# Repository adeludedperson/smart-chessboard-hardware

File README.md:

# Smart Chessboard: hardware

A 64-square chessboard that detects where pieces stand with one Hall-effect sensor per square, read by an ESP32 and sent out over USB serial or Wi-Fi.

*Render of the enclosure design for the sensing board (the renders call it "v5"). Renders, not photos.*

## What it is for

Tournament chess is played on a real board, but engines, training tools and online opponents all live on a screen. This board joins the two. You move real pieces, the board reads the position, and a chess app on a computer treats it as your move: against an engine, in a training exercise, or in a live Lichess game. The reply shows in the app and you play it on the board.

My brother plays over-the-board tournaments and practises on this board every day.

## How it works

1. **A magnet in each piece.** Each piece carries a 10 x 3 mm N35 neodymium disc in its base.
2. **A sensor under each square.** An A3144 Hall-effect switch sits at the centre of each 50 mm square, on the underside of the PCB, bent flat. The A3144 responds to one magnet pole only, so every magnet is glued with its working face down.
3. **10k pull-ups.** Each sensor output has a 10 kΩ pull-up to 3.3 V. A magnet pulls the line low, so an occupied square reads as 0.
4. **74HC165 shift registers.** Two 74HC165 parallel-in shift registers per board latch 16 sensor states at once. The registers run at 3.3 V and the sensors at 5 V, so the ESP32 never sees 5 V on a data line.
5. **Four identical boards.** The board is four 200 x 200 mm quadrant PCBs of 16 squares each, chained J2 to J1 with 6-wire jumpers. The chain carries power and signals, and the four boards together form one 64-bit shift chain.
6. **Three wires to the ESP32.** The ESP32 drives /PL (GPIO25) and CP (GPIO26) and reads the chain's data out on GPIO27. GPIO14 injects a test pattern into the chain for the gate test.
7. **USB serial or Wi-Fi out.** The firmware sends one line per frame, `raw = 0x` followed by 16 hex digits, about 50 times a second, over USB serial, or over USB and a Wi-Fi TCP connection at the same time.

In the enclosure design, the boards hang component side down on 20 mm standoffs between two 4 mm MDF sheets. The magnet sits 7.1 mm from the sensor: 4.0 mm MDF, 1.0 mm air gap, 1.6 mm PCB and about 0.5 mm into the sensor package. Dimensions, cut list, drilling, jumper lengths and assembly order are in [docs/MECHANICAL.md](docs/MECHANICAL.md).

## Hardware

| Board | What it is | Status |
|---|---|---|
| [Quadrant v1](pcb/quadrant/) | 200 x 200 mm, 2-layer, all through-hole. 16 A3144, 16 x 10k, 2 x 74HC165 (DIP-16), 10 x 100 nF, two 1x6 headers. 50 mm squares. | Fabricated (5 boards). Four assembled, chained and tested. |
| [Quadrant v2](pcb/quadrant_v2/) | 132 x 132 mm, 2-layer, all SMT for factory assembly. 33 mm squares, UHE4913G omnipolar Hall sensor and WS2812C-2020 LED per square, keyed 2x6 ribbon connectors. | Design only. DRC-clean, gerbers exported. Not ordered as of 2026-09-01. |
| [Hub v2](pcb/hub_v2/) | 88 x 60 mm. ESP32-WROOM-32E module, Micro-USB, CH340C USB-serial, TP4056 charger and 18650 holder (protected cell required). | Design only. DRC-clean, gerbers exported. Not ordered as of 2026-09-01. |
| [Hub v3 USB-C](pcb/hub_v3_usbc/) | Hub v2 with the Micro-USB port replaced by USB-C and 5.1 kΩ CC pull-downs. | Design only. DRC-clean, gerbers exported. No order recorded. |
| [RFID test rig](pcb/rfid_test_rig/) | 80 x 92 mm, 4-layer, 2x2 squares. Tests 125 kHz antenna coils under each square, an EM4095 reader and 74HC4851 muxes, toward identifying pieces as well as detecting them. | Design only. DRC-clean, gerbers exported. No order recorded. |

Notes for builders:

- The A3144 parts used on the v1 boards were mirror-pinout clones and had to go in rotated 180 degrees from a genuine part. Read [pcb/quadrant/assembly/ASSEMBLY_NOTES.md](pcb/quadrant/assembly/ASSEMBLY_NOTES.md) and solder one sensor at S0 and test it with a magnet before soldering the other 15.
- The v1 board is generated from one number, the square size. To regenerate it, follow [pcb/quadrant/README.md](pcb/quadrant/README.md).
- Design notes: [pcb/DESIGN.md](pcb/DESIGN.md) (v1), [pcb/DESIGN_V2.md](pcb/DESIGN_V2.md) (v2 compact board), [pcb/DESIGN_V3_RFID.md](pcb/DESIGN_V3_RFID.md) (RFID piece recognition, paper design).
- Per-board parts list: [pcb/quadrant/assembly/chess_quadrant_bom.csv](pcb/quadrant/assembly/chess_quadrant_bom.csv). Fasteners and wood: [docs/MECHANICAL.md](docs/MECHANICAL.md) sections 4 and 6.
- Datasheets: [A3144](https://www.allegromicro.com/en/products/sense/switches-and-latches) (Allegro, discontinued; the boards use clones), [SN74HC165](https://www.ti.com/product/SN74HC165) (TI), [ESP32](https://www.espressif.com/en/products/modules/esp32) (Espressif).

## Firmware

Arduino sketches for an ESP32 dev board, one folder per sketch in [firmware/](firmware/).

| Sketch | Use it for |
|---|---|
| `board_stream` | Main firmware, USB only. Measures the chain length at boot, streams frames at about 50 per second, re-runs the gate test every 5 s. |
| `board_stream_wifi` | Same sensing code, plus Wi-Fi: every line goes to USB serial and to a TCP connection. Adds over-the-air updates and a status page on port 80. |
| `read_audit` | Reads the board four ways and compares them. Run it before blaming a sensor. |
| `chain_len` | Counts the shift-register stages in the chain. The gate test passes on a chain that is too short; this finds it. |
| `quadrant_test`, `quadrant_diag` | Single-board bring-up. |
| `quadrant_diag32`, `quadrant_diag64` | 2-board and 4-board gate tests. |
| `dgt_clock_bridge` | A second ESP32 that connects a DGT 3000 chess clock through its 3.5 mm jack, over USB serial and Wi-Fi. |
| `adc_diag`, `rail_test`, `short_meter`, `wiring_diag`, `sensor_test`, `quad_probe`, `quadrant_diag2`, `quadrant_diag3` | One-off diagnostic rigs from bring-up. |

The gate test shifts all 0s and then all 1s through the chain and prints `CHAIN64: PASS` or `FAIL`. An all-clear frame reads the same as a dead chain, so check the gate result before trusting a reading.

[firmware/tools/](firmware/tools/) has Python serial readers and live dashboards for bring-up (no dependencies; edit the port at the top of each script).

### Flash over USB

You need `arduino-cli` with the ESP32 core. Close any program reading the serial port first.

```bash
cd firmware
arduino-cli compile --fqbn esp32:esp32:esp32 board_stream
arduino-cli upload -p <your-port> --fqbn esp32:esp32:esp32 board_stream
```

On macOS the port looks like `/dev/cu.usbserial-0001`.

### Set up Wi-Fi

1. Copy the template: `cp firmware/board_stream_wifi/secrets.example.h firmware/board_stream_wifi/secrets.h`
2. In `secrets.h`, set `WIFI_SSID` and `WIFI_PASS` (2.4 GHz networks only), `SCB_HOST` (the mDNS name of the computer that receives the stream) and `SCB_FALLBACK_IP` (that computer's address, used only on first boot). `secrets.h` is in `.gitignore`.
3. Flash once over USB: `firmware/board_stream_wifi/flash.sh <your-port>`
4. Power the ESP32 from a 5 V USB charger, 2 A or more.
5. Later updates go over Wi-Fi: `firmware/board_stream_wifi/ota.sh`

The board answers at `chess-sensor.local`, with a status page showing Wi-Fi signal, connection state and the last gate result. The helper scripts are written for macOS. The clock bridge uses the same steps in `firmware/dgt_clock_bridge/`.

## Status

- **2026-11-14:** In daily use for tournament practice.
- **2026-08-24:** Five v1 quadrant PCBs fabricated. Four assembled and chained into a 64-square board that passes the 64-stage gate test, detects a full set of 32 pieces, and streams over Wi-Fi. The wooden frame and playing surface in [docs/MECHANICAL.md](docs/MECHANICAL.md) were still listed as pending on this date.
- **2026-09-26:** DGT 3000 clock bridge tested on a real clock.
- **2026-09-26:** Quadrant v2, hub v2, hub v3 and the RFID test rig are designed and DRC-clean. No fabrication of these boards is recorded.

## Software

The board feeds a separate chess app that runs on a computer. It plays against engines (Stockfish and Maia), has training modes, and plays Lichess games from the physical board. That app is not in this repository.

## Repository layout

| Path | Contents |
|---|---|
| [pcb/](pcb/) | KiCad boards, generator and routing scripts, design notes, gerbers, BOMs, plots |
| [pcb/quadrant/assembly/](pcb/quadrant/assembly/) | Assembly notes, solder job sheets, pick-and-place, BOM |
| [firmware/](firmware/) | ESP32 sketches and the [firmware README](firmware/README.md) |
| [firmware/tools/](firmware/tools/) | Python serial readers and bring-up dashboards |
| [docs/MECHANICAL.md](docs/MECHANICAL.md) | Enclosure stack-up, cut list, drilling, wiring lengths, assembly order |
| [docs/WORKING_SETUP_2026-08-18.md](docs/WORKING_SETUP_2026-08-18.md) | Exact wiring and bit order of the first working 2-board chain |
| [docs/stickers/](docs/stickers/) | Printable 440 x 440 mm board decals, their generator and how to apply them |
| [renders/](renders/) | Renders of the board designs, including earlier LED concepts that were not built |
| [diagrams/](diagrams/) | Generator for the single-sensor test wiring diagram |
| [sim/](sim/) | SPICE model for the `short_meter` rig |

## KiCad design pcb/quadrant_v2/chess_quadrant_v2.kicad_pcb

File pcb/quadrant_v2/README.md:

# V2 Compact Quadrant — 33mm pitch, all-SMT, JLCPCB-assemblable

Generated board. **DRC clean (0 violations, 0 unconnected).**
469+ tracks, 431 vias, fully routed by `../generate_quadrant_v2.py`.

## What it is

132×132mm, 2-layer. One quadrant = 4×4 squares of the compact chessboard.
Order **20 pcs** (5 board-sets + spares), all identical.

Per square: UHE4913G omnipolar hall (C86815) at exact square center,
WS2812C-2020 RGB LED (C2976072) offset +8/+8mm, 100nF each. 2× 74HC165
(C22384789) chain all 16 sensors into the board-wide 64-bit shift chain.

## Regenerate

```
~/Applications/KiCad/KiCad.app/Contents/Frameworks/Python.framework/Versions/Current/bin/python3.9 \
    ../generate_quadrant_v2.py            # emits .kicad_pcb + BOM.csv + positions.csv
~/Applications/KiCad/KiCad.app/Contents/MacOS/kicad-cli pcb drc --severity-error \
    --format json -o drc_v2.json chess_quadrant_v2.kicad_pcb
~/Applications/KiCad/KiCad.app/Contents/MacOS/kicad-cli pcb export gerbers -o gerbers/ \
    --layers F.Cu,B.Cu,F.Paste,B.Paste,F.SilkS,B.SilkS,F.Mask,B.Mask,Edge.Cuts \
    chess_quadrant_v2.kicad_pcb
~/Applications/KiCad/KiCad.app/Contents/MacOS/kicad-cli pcb export drill -o gerbers/ \
    chess_quadrant_v2.kicad_pcb
```

## Order at JLCPCB

1. Zip `gerbers/`, upload at jlcpcb.com/quote. 132×132mm, 2-layer, 1.6mm, qty 20.
2. Enable "PCB Assembly" (economic, top side). Upload `BOM.csv` + `positions.csv`.
3. In the part-placement preview, CHECK ROTATIONS of U1-U16 (SOT-23), D1-D16
   (LED polarity dot!), U17/U18 pin-1 — JLC's rotation convention can differ
   from KiCad's. Fix in their viewer if a part looks turned.
4. Two BOM lines have no LCSC number yet — pick in JLC's picker:
   - CB1: 1000µF ≥6.3V SMT electrolytic, 8×10mm
   - J1/J2: 2×6 (12-pin) 2.54mm shrouded box header, through-hole
5. LED (C2976072) stock fluctuates; substitute WS2812B-2020 (same footprint/
   pinout) if dry.

## Interconnect (J1 = IN, top edge; J2 = OUT, bottom edge)

2×6 keyed box header + 12-way IDC ribbon. Inner row (board side) carries
signals, outer row is all GND:

| Col (left→right) | 1 | 2 | 3 | 4 | 5 | 6 |
|---|---|---|---|---|---|---|
| Inner | /PL | CP | SER | +5V | +3V3 | LED_DATA |
| Outer | GND | GND | GND | GND | GND | GND |

Chain: hub → J1 of Q1 → (J2 → next J1) ×3. Quadrants tile with alternating
180° rotation so J2/J1 meet at the seams.

## Firmware maps (printed by the generator)

```
CHAIN_ORDER (first bit read -> last) = [15,14,11,10, 2,3,6,7, 13,12,9,8, 0,1,4,5]
LED_CHAIN   (square idx, serpentine) = [0,1,2,3, 7,6,5,4, 8,9,10,11, 15,14,13,12]
```

`CHAIN_ORDER[i]` = which square (0-15, row-major from board origin) produced
the i-th bit shifted out of this quadrant. LED index k in the WS2812 chain
lights square `LED_CHAIN[k]`.

## Still manual / to verify before paying

1. Rotation check in JLC viewer (step 3 above) — the one real risk.
2. Hub PCB (ESP32 + Micro-USB + charger + 18650 holder): DONE and DRC-clean,
   see ../hub_v2/README.md.
3. First article: power one assembled quadrant alone (hub or bench 3V3/5V via
   J1) and run the firmware self-test before building all five sets.

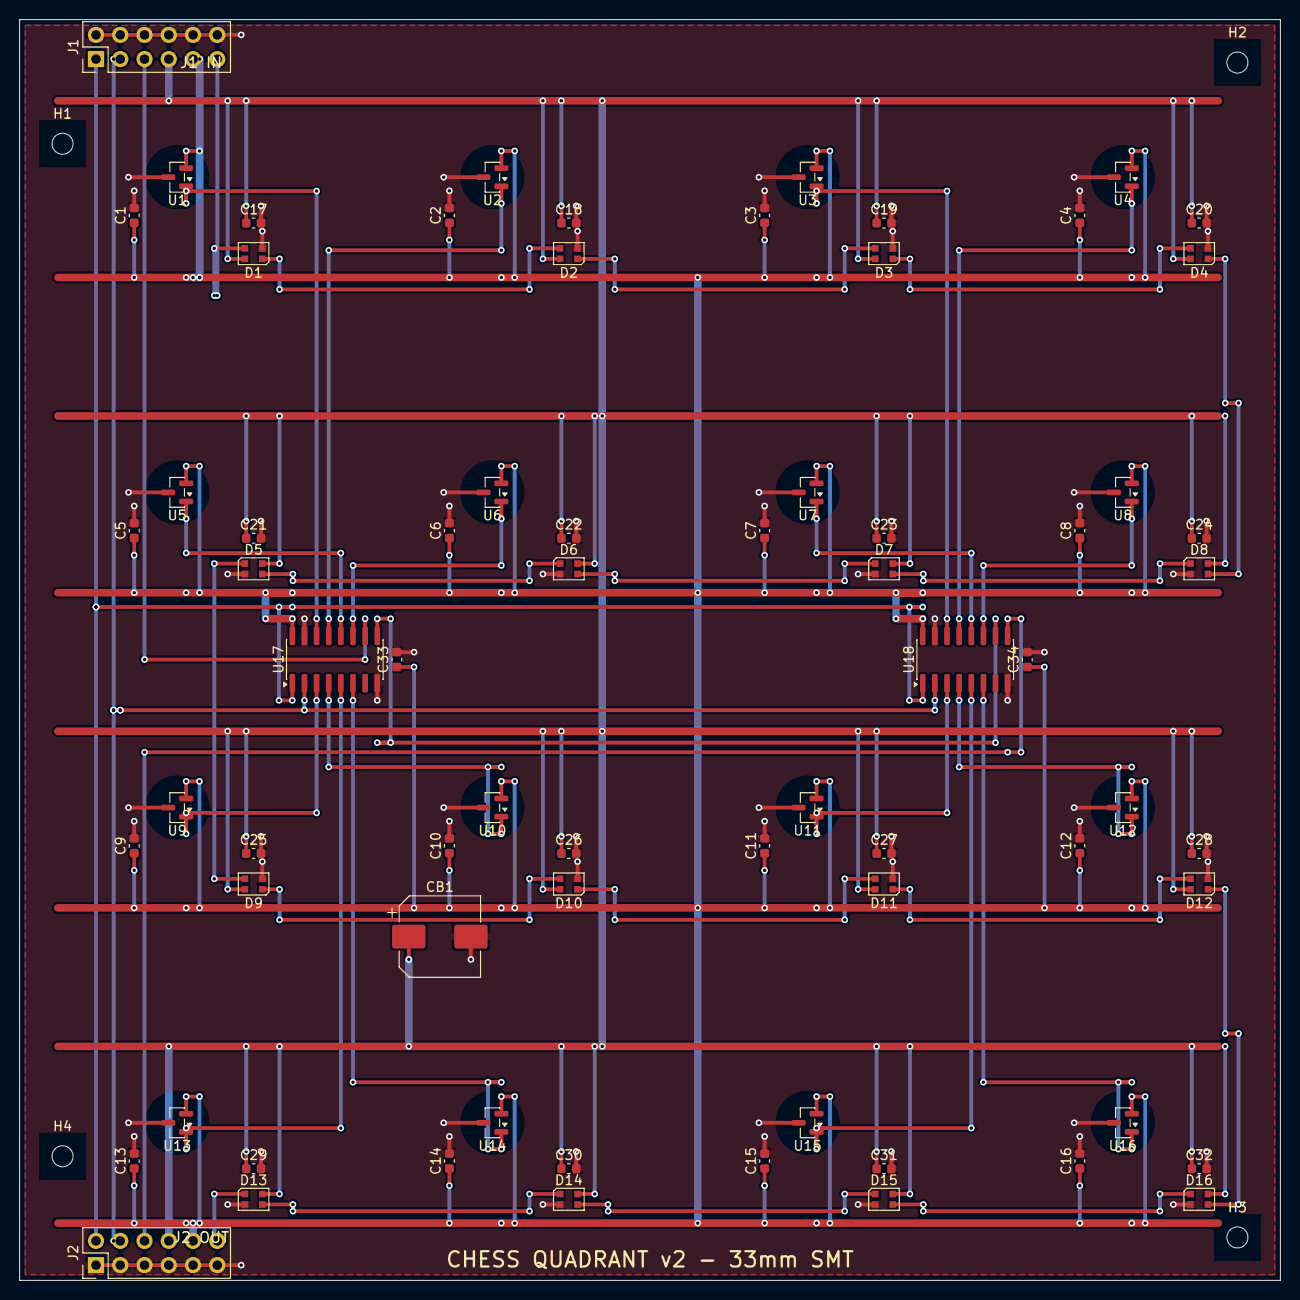
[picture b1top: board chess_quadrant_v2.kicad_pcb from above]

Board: 2 copper layers, 132.0 x 132.0 mm, 75 parts (0 on the bottom side), 41 nets.

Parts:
C1, C2, C3, C4, C5, C6, C7, C8, C9, C10, C11, C12, C13, C14, C15, C16, C17, C18, C19, C20, C21, C22, C23, C24, C25, C26, C27, C28, C29, C30, C31, C32, C33, C34: 100n; C_0603_1608Metric
CB1: 1000u/10V; CP_Elec_8x10
D1, D2, D3, D4, D5, D6, D7, D8, D9, D10, D11, D12, D13, D14, D15, D16: WS2812C-2020; LED_WS2812B-2020_PLCC4_2.0x2.0mm
H1, H2, H3, H4: MountingHole_2.2mm_M2
J1: IN; PinHeader_2x06_P2.54mm_Vertical
J2: OUT; PinHeader_2x06_P2.54mm_Vertical
U1, U2, U3, U4, U5, U6, U7, U8, U9, U10, U11, U12, U13, U14, U15, U16: UHE4913G; SOT-23
U17, U18: 74HC165; SOIC-16_3.9x9.9mm_P1.27mm

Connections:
+3V3: C1.1, C2.1, C3.1, C4.1, C5.1, C6.1, C7.1, C8.1, C9.1, C10.1, C11.1, C12.1, C13.1, C14.1, C15.1, C16.1, C33.1, C34.1, J1.9, J2.10, U1.2, U2.2, U3.2, U4.2, U5.2, U6.2, U7.2, U8.2, U9.2, U10.2, U11.2, U12.2, U13.2, U14.2, U15.2, U16.2, U17.16, U18.16
+5V: C17.1, C18.1, C19.1, C20.1, C21.1, C22.1, C23.1, C24.1, C25.1, C26.1, C27.1, C28.1, C29.1, C30.1, C31.1, C32.1, CB1.1, D1.4, D2.4, D3.4, D4.4, D5.4, D6.4, D7.4, D8.4, D9.4, D10.4, D11.4, D12.4, D13.4, D14.4, D15.4, D16.4, J1.7, J2.8
/PL: J1.1, J2.2, U17.1, U18.1
CP: J1.3, J2.4, U17.2, U18.2
GND: C1.2, C2.2, C3.2, C4.2, C5.2, C6.2, C7.2, C8.2, C9.2, C10.2, C11.2, C12.2, C13.2, C14.2, C15.2, C16.2, C17.2, C18.2, C19.2, C20.2, C21.2, C22.2, C23.2, C24.2, C25.2, C26.2, C27.2, C28.2, C29.2, C30.2, C31.2, C32.2, C33.2, C34.2, CB1.2, D1.2, D2.2, D3.2, D4.2, D5.2, D6.2, D7.2, D8.2, D9.2, D10.2, D11.2, D12.2, D13.2, D14.2, D15.2, D16.2, J1.2, J1.4, J1.6, J1.8, J1.10, J1.12, J2.1, J2.3, J2.5, J2.7, J2.9, J2.11, U1.3, U2.3, U3.3, U4.3, U5.3, U6.3, U7.3, U8.3, U9.3, U10.3, U11.3, U12.3, U13.3, U14.3, U15.3, U16.3, U17.8, U17.15, U18.8, U18.15
LEDD_0: D1.3, J1.11
LEDD_1: D1.1, D2.3
LEDD_2: D2.1, D3.3
LEDD_3: D3.1, D4.3
LEDD_4: D4.1, D8.3
LEDD_5: D7.3, D8.1
LEDD_6: D6.3, D7.1
LEDD_7: D5.3, D6.1
LEDD_8: D5.1, D9.3
LEDD_9: D9.1, D10.3
LEDD_10: D10.1, D11.3
LEDD_11: D11.1, D12.3
LEDD_12: D12.1, D16.3
LEDD_13: D15.3, D16.1
LEDD_14: D14.3, D15.1
LEDD_15: D13.3, D14.1
LEDD_16: D13.1, J2.12
SENS_0: U1.1, U17.14
SENS_1: U2.1, U17.13
SENS_2: U3.1, U18.14
SENS_3: U4.1, U18.13
SENS_4: U5.1, U17.12
SENS_5: U6.1, U17.11
SENS_6: U7.1, U18.12
SENS_7: U8.1, U18.11
SENS_8: U9.1, U17.3
SENS_9: U10.1, U17.4
SENS_10: U11.1, U18.3
SENS_11: U12.1, U18.4
SENS_12: U13.1, U17.5
SENS_13: U14.1, U17.6
SENS_14: U15.1, U18.5
SENS_15: U16.1, U18.6
SER_IN: J1.5, U17.10
SER_MID: U17.9, U18.10
SER_OUT: J2.6, U18.9

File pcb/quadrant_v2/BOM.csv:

Comment,Designator,Footprint,LCSC Part #
1000u/10V,CB1,CP_Elec_8x10,C5246577
100n,"C1,C2,C3,C4,C5,C6,C7,C8,C9,C10,C11,C12,C13,C14,C15,C16,C17,C18,C19,C20,C21,C22,C23,C24,C25,C26,C27,C28,C29,C30,C31,C32,C33,C34",C_0603_1608Metric,C5137636
74HC165,"U17,U18",SOIC-16_3.9x9.9mm_P1.27mm,C22384789
2x6 header,"J1,J2",PinHeader_2x06_P2.54mm_Vertical,C7501277
UHE4913G,"U1,U2,U3,U4,U5,U6,U7,U8,U9,U10,U11,U12,U13,U14,U15,U16",SOT-23,C86815
WS2812C-2020,"D1,D2,D3,D4,D5,D6,D7,D8,D9,D10,D11,D12,D13,D14,D15,D16",LED_WS2812B-2020_PLCC4_2.0x2.0mm,C52917434

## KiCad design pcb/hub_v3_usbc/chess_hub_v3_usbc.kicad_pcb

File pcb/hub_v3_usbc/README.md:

# Hub V3 — 88×60mm, ESP32 + **USB-C** + CH340C + TP4056 + 18650

**Status: DONE, DRC-clean.** 0 errors, 0 unconnected items, 4 cosmetic silk
warnings (the same SW1/BT1 overhangs hub_v2 has). 223 tracks + 323 vias,
2-layer, GND pour both sides. Gerbers + drill in `gerbers/`, ready to zip.

This is **hub_v2 with the Micro-USB port replaced by USB-C.** Nothing else on
the board changed — same placement, same GPIO map, same power tree. It was
re-autorouted from scratch because the connector's pad field moved.

`../hub_v2/` is untouched and still valid if you'd rather build the
micro-USB version.

## Ordering note — BT1 is hand-fitted, not assembled by JLC

`BOM.csv` deliberately omits **BT1 (18650 holder)**. The only JLC part matching
the Keystone 1042 land pattern is C5249310: $4.85/pc, **sold in 50-pc reels**
(~$242 for a 5-board run) and flagged **Standard Only**, which would force the
whole order off Economic assembly. Buy a holder locally and solder the two
pads by hand.

Parts picked for the previously-blank BOM lines (verified in stock against
JLCPCB's live parts API, 2026-09-04):

| Ref | Part | LCSC | Stock |
|---|---|---|---|
| SW2, SW3 | C&K PTS645SM43SMTR92LFS tact | C221880 | 4,014 |
| SW1 | C&K PCM12SMTR slide switch | C221841 | 801 |
| J1 | ZX-PZ2.54-2-6PZZ 2x6 header | C7501277 | 35,112 |

SW2/SW3 are one merged BOM line — JLCPCB rejects two lines matched to the same
part ("Multiple lines in the BOM have been matched to the same part").

⚠️ Verify SW1: KiCad's `SW_SPDT_PCM12` says right-angle, JLC's attribute table
says vertical. Check against C&K's `pcm.pdf` land pattern before paying.

---

## What changed vs hub_v2

| | hub_v2 | hub_v3_usbc |
|---|---|---|
| Connector | USB Micro-B, Wuerth 629105150521 land pattern | **USB-C 16-pin receptacle**, HRO `TYPE-C-31-M-12` land pattern |
| Connector position | USB1 @ (36.00, 3.45) rot 0 | USB1 @ (35.50, 3.90) **rot 180** (mouth faces the top edge, 0.25mm inside it) |
| CC pulldowns | n/a | **R8, R9 — 5.1kΩ 0603**, CC1→GND and CC2→GND |
| Net count | — | +2 nets (`CC1`, `CC2`) |
| Net classes | Default / Power / VBUS | + **`USB_C`** (0.20mm track, 0.15mm clearance) for UDP, UDM, CC1, CC2 |
| Zone pours | 0.35mm clearance, 0.25mm min neck | 0.25mm clearance, 0.20mm min neck (see below) |
| BOM | 21 lines | 22 lines (USB-C, 5k1 ×2; MicroUSB gone) |

### Why the 5.1k resistors are not optional

A USB-C **source** keeps VBUS off until it sees a sink advertise itself by
pulling CC to ground through 5.1kΩ (Rd). Without R8/R9 a USB-C charger or a
USB-C laptop port supplies **nothing** — the board would only charge from a
legacy USB-A→C cable, which has its own resistor in the plug. Both CC1 and CC2
get their own resistor (never one shared resistor across both), so the cable
works either way up.

### USB 2.0 wiring, both orientations

The receptacle has duplicate differential pairs so it works flipped. This is a
USB 2.0-only design, so the duplicates are shorted on the board:

| Receptacle pins | Net | Goes to |
|---|---|---|
| A1, B1, A12, B12 + 4 shield legs | GND | pour |
| A4, B4, A9, B9 | VBUS | D1 (SS34), TP4056 IN, C5, R6 |
| A6 + B6 (DP1, DP2) | UDP | CH340C pin 5 |
| A7 + B7 (DN1, DN2) | UDM | CH340C pin 6 |
| A5 | CC1 | R8 → GND |
| B5 | CC2 | R9 → GND |
| A8, B8 (SBU1, SBU2) | *not connected* | — |

No PD, no alt-mode, no SBU. 5V @ whatever the source gives on a plain
Rd-only sink — plenty for the TP4056's 1A charge current.

### How the 0.5mm-pitch fanout was solved

This is the thing that got USB-C deferred out of v2. The escape works because
the connector is a **single-row 12-position** footprint, so nothing needs a
diagonal via fan-out — but D+ and D− still interleave
(`… B6/DP2 · A7/DN1 · A6/DP1 · B7/DN2 …`), so the two duplicate pairs cross.

The crossing is resolved **without a single via**:

* **UDP** (34.75 and 35.75) is shorted *behind* the pad row, at y ≈ 8.9.
* **UDM** (35.25 and 36.25) is shorted *in front of* the pad row, at y ≈ 6.95,
  under the connector's plastic pin block. Safe: the pad row itself already
  extends 0.33mm under the body outline, so nothing conductive presses down
  there, and the trace is under solder mask.

0.20mm tracks out of the 0.30mm pads leave 0.25mm to each neighbouring pad,
against a 0.15mm rule — that's what the `USB_C` net class is for. VBUS keeps
its own 0.40mm class (0.80mm cannot escape a 0.60mm pad).

CC1 drops straight down 1.9mm into R8; CC2 straight down into R9.

### Zone clearance change

hub_v2's pours used a 0.35mm zone clearance and a 0.25mm minimum neck. With
more copper pushed through the middle of the board, that pinched the F.Cu pour
into islands around U2 pad 1 and C5 pad 2 that no stitching via could reach.
Pours are now 0.25mm / 0.20mm — still above the 0.20mm netclass clearance and
far above JLC's 0.127mm minimum. F.Cu is a single connected region again.

---

## Everything else (unchanged from hub_v2)

- ESP32-WROOM-32E top-left, antenna keepout (x 6.5–25.5, y 1–9.2) copper-free
  and still enforced — the USB-C sits at x ≥ 30.1 and does not encroach.
  Espressif's *full* keepout is unsatisfiable on an 88×60 outline; the
  board-level one is the rule that is checked and it passes.
- CH340C USB-UART, TP4056 charger + SMT 18650 holder — **USE A PROTECTED
  CELL**, there is no DW01 on the board.
- AMS1117-3.3, SS34 diode-OR (VBUS/VBAT → VSYS), PCM12 slide switch (right
  edge), EN + BOOT tactile buttons, power + charge LEDs.
- **No autoboot transistors.** First flash: hold BOOT, tap EN, release BOOT,
  then upload. Everything after that is OTA.
- LED_5V = VSYS, no boost.
- J1 (2×6, top right): inner row /PL CP SER +5V(VSYS) +3V3 LED_DATA, outer row
  all GND.
- GPIO map: /PL=25, CP=26, SER=14, LED_DATA=27 via a 74AHCT1G125 buffer.

### Net classes (`chess_hub_v3_usbc.kicad_pro`)

| Class | Nets | Track | Clearance | Via |
|---|---|---|---|---|
| Default | signals | 0.30mm | 0.20mm | 0.6/0.3 |
| Power | GND, VSYS, BATP, VSW, +3V3 | 0.80mm | 0.20mm | 0.8/0.4 |
| VBUS | VBUS | 0.40mm | 0.20mm | 0.6/0.3 |
| USB_C | UDP, UDM, CC1, CC2 | 0.20mm | 0.15mm | 0.6/0.3 |

Board minimums: 0.15mm clearance, 0.20mm track, 0.30mm hole, 0.50mm copper-to-edge.

---

## Parts (new lines only)

| Ref | Value | Footprint | LCSC | JLC library | Price |
|---|---|---|---|---|---|
| USB1 | USB-C | `USB_C_Receptacle_HRO_TYPE-C-31-M-12` | **C165948** | Extended | **$0.185 @1, $0.103 @1k** (≈₹16 each at qty 5) |
| R8, R9 | 5k1 | `R_0603_1608Metric` | **C23186** | Basic | ~$0.002 |

**There is no Basic-library USB-C receptacle at JLCPCB** — a search of their
base library returns zero Type-C parts, so any USB-C here is an Extended part.
C165948 is "Economic and Standard" assembly eligible, 300k+ in stock.

Cheaper drop-in candidate: **C2765186** (SHOU HAN `TYPE-C 16PIN 2MD(073)`,
$0.074 @1, 1M+ stock, also Economic-eligible). Same 16-pin single-row family,
but **check its shield-leg hole positions against this footprint before
substituting** — this board is drawn to the HRO 31-M-12 land pattern.

Net cost delta vs hub_v2: about **+$0.19 per board** (connector + 2 resistors,
minus the micro-USB you no longer buy), plus one more unique part on the feeder.

---

## How it was built

```
KP=~/Applications/KiCad/KiCad.app/Contents/Frameworks/Python.framework/Versions/Current/bin/python3.9

cp -R pcb/hub_v2 pcb/hub_v3_usbc          # then rename chess_hub_v2.* -> chess_hub_v3_usbc.*
$KP ../swap_usbc_v3.py                     # micro-USB out, USB-C + R8/R9 in, rip up all copper
$KP -c "import pcbnew; b=pcbnew.LoadBoard('chess_hub_v3_usbc.kicad_pcb'); \
        pcbnew.ZONE_FILLER(b).Fill(b.Zones()); b.Save('chess_hub_v3_usbc.kicad_pcb'); \
        pcbnew.ExportSpecctraDSN(b,'/tmp/hubc.dsn')"
java -jar freerouting-1.9.0.jar -de /tmp/hubc.dsn -do /tmp/hubc.ses -mp 30
$KP ../route_hub_v3.py /tmp/hubc.ses       # import, 3mm GND stitch grid, refill, emit CSVs
$KP ../stitch_gnd_v3.py                    # loosen pours to 0.25/0.20, stitch the last islands
$KP ../fix_silk_v3.py                      # pull USB1 silk off the board edge, move ref fields
```

FreeRouting **1.9.0**, not 2.x — the 2.x jars need Java 25 and the JDK here is
Temurin 21. Auto-route took 0.9s, optimisation 12s.

Gerbers:

```
CLI=~/Applications/KiCad/KiCad.app/Contents/MacOS/kicad-cli
$CLI pcb export gerbers --output gerbers/ \
     --layers "F.Cu,B.Cu,F.Paste,B.Paste,F.Silkscreen,B.Silkscreen,F.Mask,B.Mask,Edge.Cuts" \
     chess_hub_v3_usbc.kicad_pcb
$CLI pcb export drill --output gerbers/ --format excellon --drill-origin absolute \
     --excellon-units mm --excellon-zeros-format decimal chess_hub_v3_usbc.kicad_pcb
$CLI pcb drc --severity-error --format json -o /tmp/drc.json chess_hub_v3_usbc.kicad_pcb
```

### Do not re-run `../generate_hub_v2.py`

It has a DO-NOT-RUN header and four known bugs, and it targets `hub_v2/`
anyway. All hub edits go through load/modify/save scripts like the three above.

## Remaining DRC warnings (4, all cosmetic)

SW1 and BT1 footprint silkscreen crosses the board outline — both parts
overhang the edge by design (switch actuator, battery holder body). JLC clips
silk at the edge. Identical to hub_v2.

## Order at JLCPCB

1. Zip `gerbers/`, upload at jlcpcb.com/quote. 88×60mm, 2-layer, 1.6mm, qty 5.
2. Enable PCB Assembly (economic, top side). Upload `BOM.csv` + `positions.csv`.
   J1 and BT1 are through-hole and are deliberately left out of
   `positions.csv` — fit them by hand or pay for THT assembly.
3. **Check rotations in the placement preview**: U1 pin 1, U2/U3 pin 1,
   D1/D2 cathode band, LED1/LED2 polarity, and **USB1 — it is placed at 180°**,
   mouth toward the board's top edge. JLC's rotation convention differs from
   KiCad's; a flipped USB-C is a dead board.
4. BOM lines with no LCSC number, pick in their picker: BT1 (Keystone
   1042-compatible SMT 18650 holder), J1 (2×6 2.54mm shrouded box header),
   SW1 (PCM12 SPDT slide switch), SW2/SW3 (PTS645 6mm tactile).
5. Enclosure note: the receptacle mouth sits 0.25mm inside the top board edge,
   so the case cutout must be flush with that edge — the plug body cannot be
   recessed behind it.

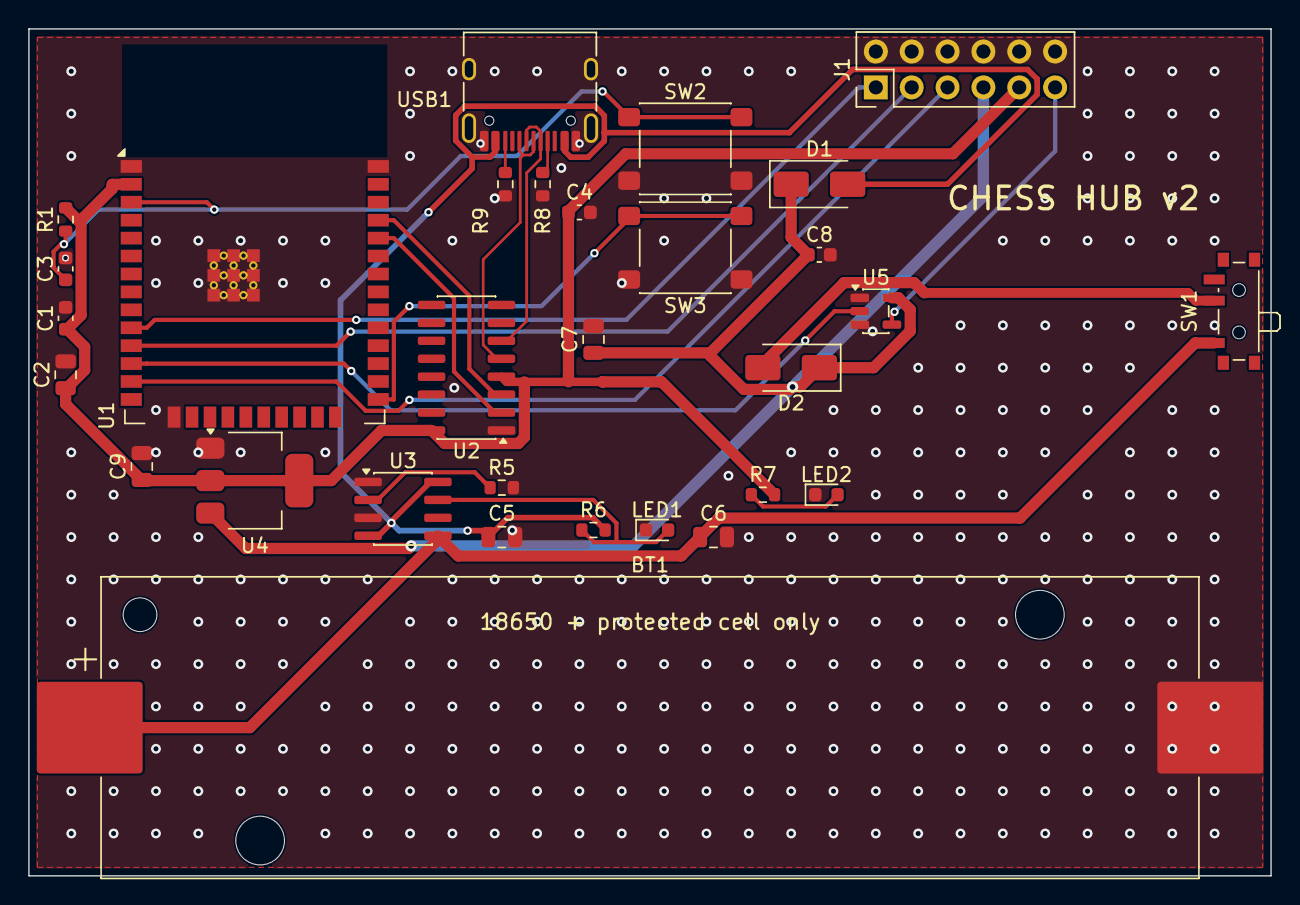
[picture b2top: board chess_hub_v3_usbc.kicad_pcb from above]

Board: 2 copper layers, 88.0 x 60.0 mm, 30 parts (0 on the bottom side), 22 nets.

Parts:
BT1: 18650; BatteryHolder_Keystone_1042_1x18650
C1, C4, C8: 100n; C_0603_1608Metric
C2, C5, C6, C7, C9: 10u; C_0805_2012Metric
C3: 1u; C_0603_1608Metric
D1, D2: SS34; D_SMA
J1: OUT; PinHeader_2x06_P2.54mm_Vertical
LED1: CHG; LED_0603_1608Metric
LED2: PWR; LED_0603_1608Metric
R1: 10k; R_0603_1608Metric
R5: 2k; R_0603_1608Metric
R6, R7: 1k; R_0603_1608Metric
R8, R9: 5k1; R_0603_1608Metric
SW1: PWR_SLIDE; SW_SPDT_PCM12
SW2: EN; SW_SPST_PTS645Sx43SMTR92
SW3: BOOT; SW_SPST_PTS645Sx43SMTR92
U1: ESP32-WROOM-32E
U2: CH340C; SOIC-16_3.9x9.9mm_P1.27mm
U3: TP4056; SOIC-8_3.9x4.9mm_P1.27mm
U4: AMS1117-3.3; SOT-223-3_TabPin2
U5: 74AHCT1G125; SOT-23-5
USB1: USB-C; USB_C_Receptacle_HRO_TYPE-C-31-M-12

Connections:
+3V3: C1.1, C2.1, C4.1, C9.1, J1.9, R1.2, R7.2, U1.2, U2.4, U2.16, U4.2
/PL: J1.1, U1.10
BATP: BT1.1, C6.1, SW1.1, U3.5
CC1: R8.1, USB1.A5
CC2: R9.1, USB1.B5
CHRGK: LED1.2, R6.1, U3.7
CP: J1.3, U1.11
EN: C3.1, R1.1, SW2.1, U1.3
G27: U1.12, U5.2
GND: BT1.2, C1.2, C2.2, C3.2, C4.2, C5.2, C6.2, C7.2, C8.2, C9.2, J1.2, J1.4, J1.6, J1.8, J1.10, J1.12, LED1.1, LED2.1, R5.2, R8.2, R9.2, SW2.2, SW3.2, U1.1, U1.15, U1.38, U1.39, U2.1, U3.1, U3.3, U4.1, U5.1, U5.3, USB1.A1, USB1.A12, USB1.B1, USB1.B12, USB1.SH
IO0: SW3.1, U1.25
LEDD: J1.11, U5.4
PROG: R5.1, U3.2
PWRK: LED2.2, R7.1
RXD0: U1.34, U2.2
SER: J1.5, U1.13
TXD0: U1.35, U2.3
UDM: U2.6, USB1.A7, USB1.B7
UDP: U2.5, USB1.A6, USB1.B6
VBUS: C5.1, D1.2, R6.2, U3.4, U3.8, USB1.A4, USB1.A9, USB1.B4, USB1.B9
VSW: D2.2, SW1.2
VSYS: C7.1, C8.1, D1.1, D2.1, J1.7, U4.3, U5.5

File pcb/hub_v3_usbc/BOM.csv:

Comment,Designator,Footprint,LCSC Part #
100n,"C1,C4,C8",C_0603_1608Metric,C5137636
10k,R1,R_0603_1608Metric,C25804
10u,"C2,C5,C6,C7,C9",C_0805_2012Metric,C15850
1k,"R6,R7",R_0603_1608Metric,C21190
1u,C3,C_0603_1608Metric,C15849
2k,R5,R_0603_1608Metric,C22975
5k1,"R8,R9",R_0603_1608Metric,C23186
74AHCT1G125,U5,SOT-23-5,C7470
AMS1117-3.3,U4,SOT-223-3_TabPin2,C6186
TACT,"SW3,SW2",SW_SPST_PTS645Sx43SMTR92,C221880
CH340C,U2,SOIC-16_3.9x9.9mm_P1.27mm,C84681
CHG,LED1,LED_0603_1608Metric,C2286
ESP32-WROOM-32E,U1,ESP32-WROOM-32E,C701341
OUT,J1,PinHeader_2x06_P2.54mm_Vertical,C7501277
PWR,LED2,LED_0603_1608Metric,C221904
PWR_SLIDE,SW1,SW_SPDT_PCM12,C221841
SS34,"D1,D2",D_SMA,C8678
TP4056,U3,SOIC-8_3.9x4.9mm_P1.27mm,C725790
USB-C,USB1,USB_C_Receptacle_HRO_TYPE-C-31-M-12,C165948

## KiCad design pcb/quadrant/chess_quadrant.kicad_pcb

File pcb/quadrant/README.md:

# Chess Quadrant PCB — generated board

**Status: READY TO ORDER.** Pitch finalized at **50.0mm** (2026-07-27) → board is **200×200mm**. DRC clean: 0 violations, 0
unconnected items. Sensor pad mirroring verified against live pcbnew.

> **2026-07-27 — sensor flip bug fixed.** `place()` in `generate_quadrant.py`
> called `SetOrientationDegrees(rot)` *after* `Flip()`, which overwrote the
> mirror and left all 16 A3144 footprints tagged B.Cu with **un-mirrored pad
> geometry** (S0 pads read +5V/GND/SENS at x = 23.73/25.00/26.27 — same order as
> the un-flipped library part, i.e. VCC and OUT swapped on the real board).
> Fix: rotate *before* flipping. S0 now reads 26.27/25.00/23.73 (reversed).
> **Any gerbers exported before 2026-07-27 22:00 are dead — do not fab them.**
> Current `gerbers/chess_quadrant_gerbers_50mm.zip` contains the fix.

## What this is

One 4×4 sensor quadrant (200×200mm at 50mm pitch). The full board = 4 of these
daisy-chained J2→J1 in an S-pattern. 2-layer, all through-hole, GND pour both
sides.

- 16× A3144 hall sensor (TO-92) — **soldered on the BACK** (S0–S15 silk on back),
  at exact square centers, 8mm copper keep-out ring around each
- 16× 10kΩ pull-up (R0–R15), SENS → +3V3
- 2× 74HC165 (U1 serves sensor cols 0-1, U2 cols 2-3), VCC=3.3V, CE=GND
- 10× 100nF (C0–C7 on 5V rails, C8/C9 at registers)
- J1 (IN, left edge) / J2 (OUT, right edge): `5V | 3V3 | GND | /PL | CP | SER`
- 4× M2 mounting holes

## Firmware bit order (per quadrant)

Chain: J1.SER → U1.DS, U1.Q7 → U2.DS, U2.Q7 → J2 (next quadrant / ESP32).
First bit clocked out = U2.D7 … last = U1.D0. Sensor index for each bit:

```python
# bit position in 16-bit read -> sensor number (S0..S15, row*4+col)
CHAIN_ORDER = [15, 14, 11, 10, 2, 3, 6, 7, 13, 12, 9, 8, 0, 1, 4, 5]
```

(Printed by the generator on every run — re-copy it if you change the layout.)

## Regenerate (pitch is already final at 50.0 — only change if the wood changes)

```bash
cd pcb
KPY=~/Applications/KiCad/KiCad.app/Contents/Frameworks/Python.framework/Versions/3.9/bin/python3.9
CLI=~/Applications/KiCad/KiCad.app/Contents/MacOS/kicad-cli

$KPY generate_quadrant.py 50.0                    # prints CHAIN_ORDER
$KPY verify_flip.py                               # pad-mirror + net audit, must say PASS
$CLI pcb drc --severity-error --format json \
  --output quadrant/drc.json quadrant/chess_quadrant.kicad_pcb
cd quadrant
$CLI pcb export gerbers --output gerbers/ \
  --layers F.Cu,B.Cu,F.Mask,B.Mask,F.Silkscreen,B.Silkscreen,Edge.Cuts \
  chess_quadrant.kicad_pcb
$CLI pcb export drill --output gerbers/ --format excellon chess_quadrant.kicad_pcb
cd gerbers && zip -X chess_quadrant_gerbers_50mm.zip \
  chess_quadrant-*.gbl chess_quadrant-*.gbs chess_quadrant-*.gbo \
  chess_quadrant-*.gm1 chess_quadrant-*.gtl chess_quadrant-*.gts \
  chess_quadrant-*.gto chess_quadrant-job.gbrjob chess_quadrant.drl
```

Everything derives from that one number. Board outline = 4 × pitch, square.
**Always re-run `verify_flip.py` after regenerating** — it is the guard against
the sensor mirror bug coming back.

## Files

- `chess_quadrant.kicad_pcb` — open in KiCad (PCB Editor.app) to inspect
- `gerbers/chess_quadrant_gerbers_50mm.zip` — upload this to the fab
- `drc.json` — last DRC run (0 violations, 0 unconnected)
- `plots/board_50mm.pdf` — print at 1:1 for the overlay check
- `plots/render_top_50mm.png`, `plots/render_bottom_50mm.png`
- `../verify_flip.py` — pad-mirror / net / edge-cuts / ratsnest audit

## Pre-order checklist

Machine-verified (re-checked 2026-07-27 after the flip fix):

1. [x] Square size finalized at **50.0mm** → regenerated, board 200×200mm
   (Edge_Cuts gerber measured: 200.000 × 200.000mm)
2. [x] **DRC clean** — 0 violations, 0 unconnected (`drc.json`)
3. [x] **Sensor pad mirror verified** — all 16 A3144 on B.Cu with reversed pad
   x-order (`verify_flip.py` → PASS); 10k pull-ups and caps still on the right
   nets, everything else on F.Cu

Still needs a human:

4. [ ] **Print `plots/board_50mm.pdf` at 1:1**, lay it under the actual wooden
   board, confirm sensor circles land at square centers
5. [ ] Re-upload `gerbers/chess_quadrant_gerbers_50mm.zip` to Lion Circuits
   (dimensions unchanged, so the ₹6,728 qty-5 quote should hold) → confirm
   price, then order

## Design notes / gotchas

- Sensor +5V feed tracks are 0.5mm (6mA per sensor — fine); rails are 1.0mm.
- Sensor GND pin escapes the pour keep-out via a stub + via just outside the
  8mm ring.
- The DIP-16s sit in the horizontal center lane; control signals (/PL, CP,
  SER chain) run in corridors between the two DIP pad rows.
- Pull-ups are at `y = square_center + 10mm`, inside the inter-square lane.
- A3144 pinout (flat face toward you, legs down): 1=VCC, 2=GND, 3=OUT.
  On this footprint pad 1 = +5V, pad 2 = GND (center), pad 3 = SENS.
- **Assembly (CORRECTED 2026-08 — this supersedes older text):** sensors mount
  on the BACK. These clones are TRUE MIRROR-PINOUT parts — orient each TO-92
  with its **TEXT/printed side facing the FLAT side of the silkscreen outline**
  (180° rotated vs a genuine part). After soldering, **bend the body 90° flat
  against the PCB, text face touching the board**. See `../DESIGN.md` sensor
  assembly rule.
- The footprint is mirrored onto B.Cu, so on the back side pad 1 (+5V) sits to
  the **right** of center and pad 3 (SENS) to the left (viewed from the back).

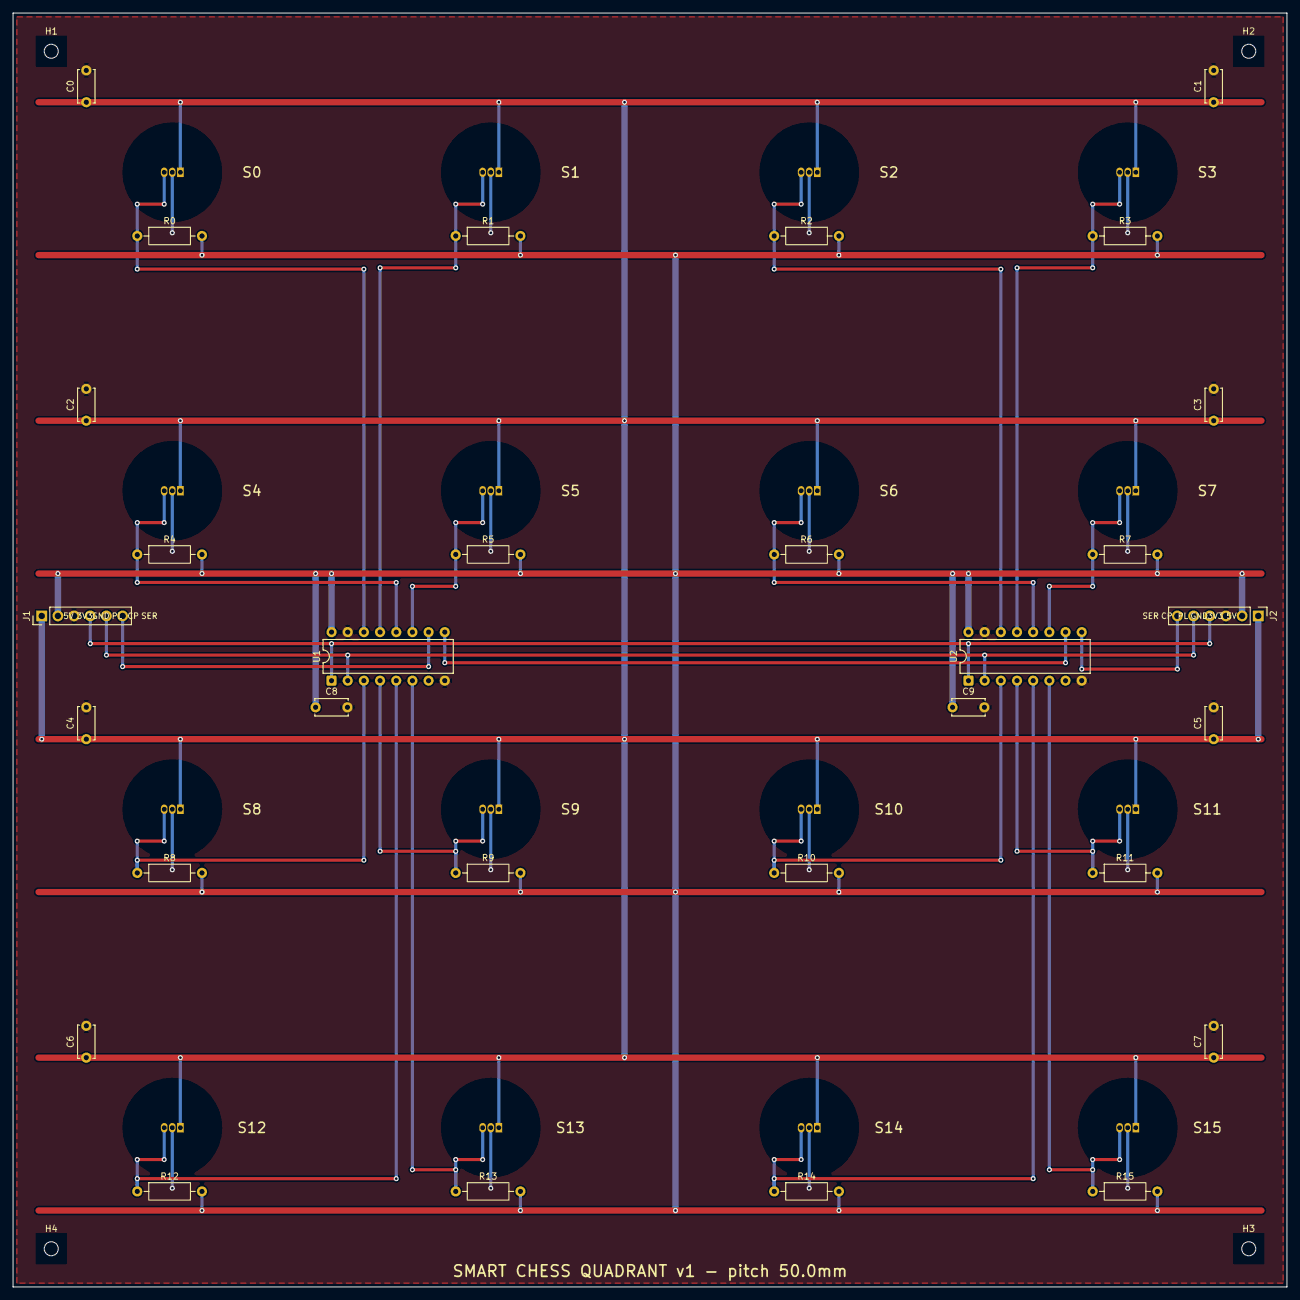
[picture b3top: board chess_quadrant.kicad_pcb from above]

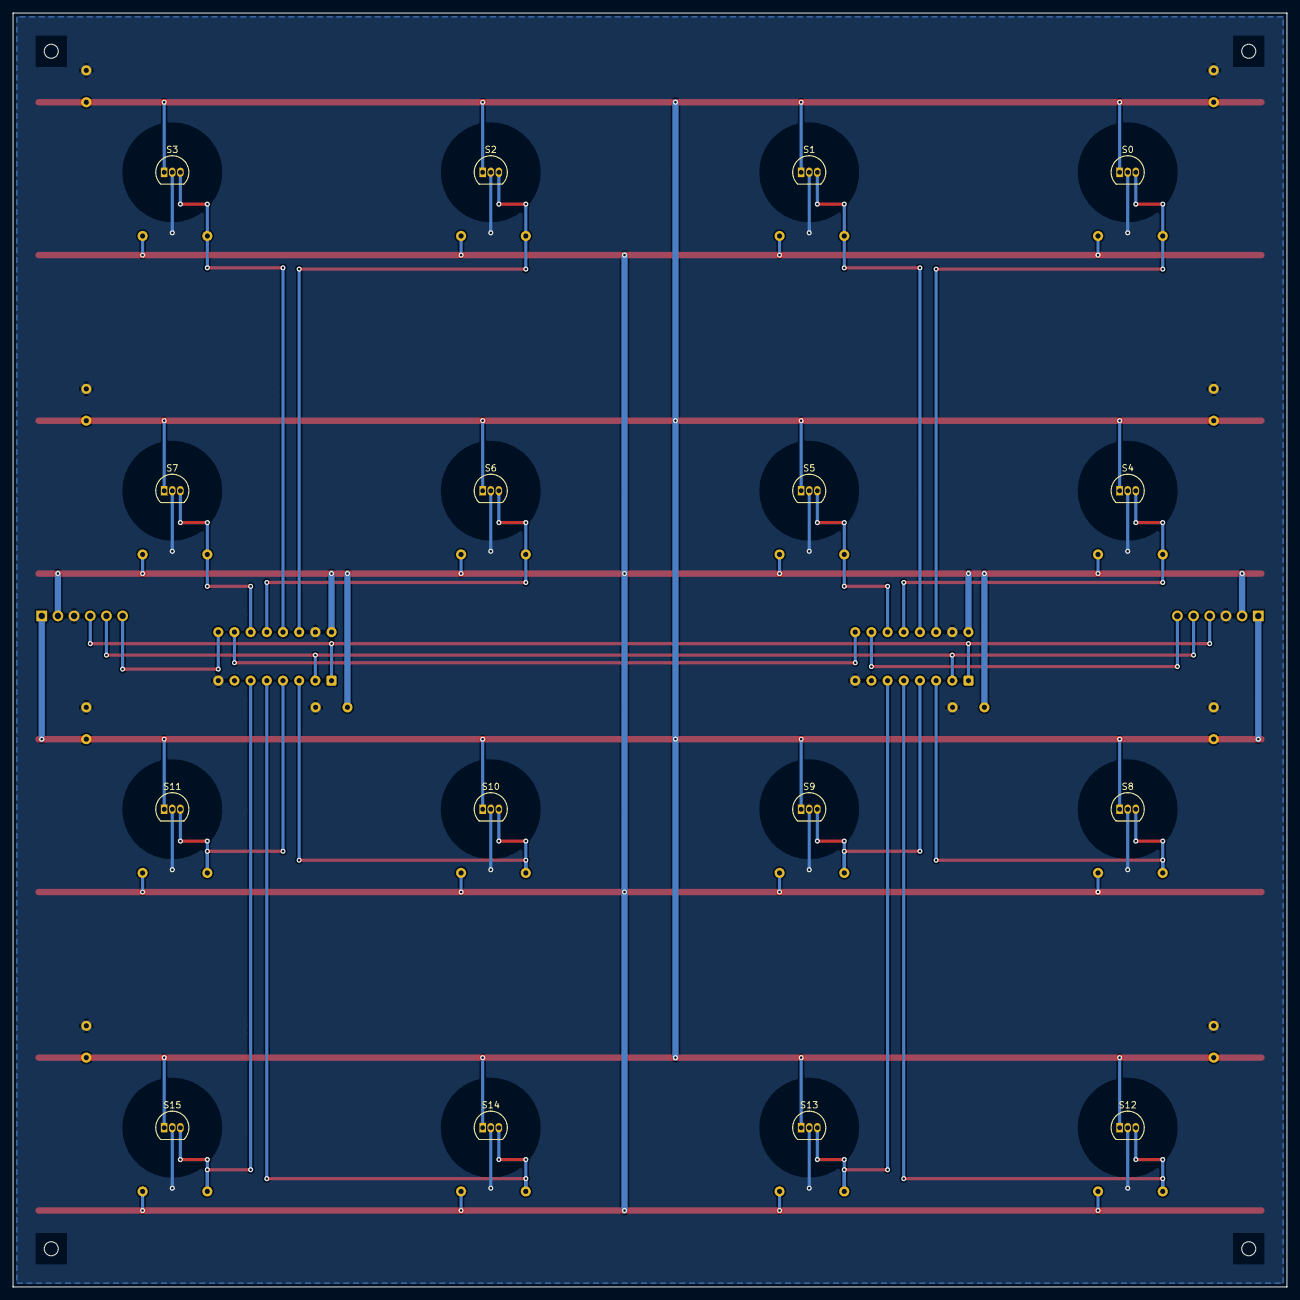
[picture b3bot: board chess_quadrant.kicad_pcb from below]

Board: 2 copper layers, 200.0 x 200.0 mm, 50 parts (16 on the bottom side), 24 nets.

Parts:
C0, C1, C2, C3, C4, C5, C6, C7, C8, C9: 100n; C_Disc_D5.0mm_W2.5mm_P5.00mm
H1, H2, H3, H4: MountingHole_2.2mm_M2
J1: IN; PinHeader_1x06_P2.54mm_Vertical
J2: OUT; PinHeader_1x06_P2.54mm_Vertical
R0, R1, R2, R3, R4, R5, R6, R7, R8, R9, R10, R11, R12, R13, R14, R15: 10k; R_Axial_DIN0207_L6.3mm_D2.5mm_P10.16mm_Horizontal
S0, S1, S2, S3, S4, S5, S6, S7, S8, S9, S10, S11, S12, S13, S14, S15: A3144; TO-92_Inline
U1, U2: 74HC165; DIP-16_W7.62mm

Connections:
+3V3: C8.1, C9.1, J1.2, J2.2, R0.2, R1.2, R2.2, R3.2, R4.2, R5.2, R6.2, R7.2, R8.2, R9.2, R10.2, R11.2, R12.2, R13.2, R14.2, R15.2, U1.16, U2.16
+5V: C0.1, C1.1, C2.1, C3.1, C4.1, C5.1, C6.1, C7.1, J1.1, J2.1, S0.1, S1.1, S2.1, S3.1, S4.1, S5.1, S6.1, S7.1, S8.1, S9.1, S10.1, S11.1, S12.1, S13.1, S14.1, S15.1
/PL: J1.4, J2.4, U1.1, U2.1
CP: J1.5, J2.5, U1.2, U2.2
GND: C0.2, C1.2, C2.2, C3.2, C4.2, C5.2, C6.2, C7.2, C8.2, C9.2, J1.3, J2.3, S0.2, S1.2, S2.2, S3.2, S4.2, S5.2, S6.2, S7.2, S8.2, S9.2, S10.2, S11.2, S12.2, S13.2, S14.2, S15.2, U1.8, U1.15, U2.8, U2.15
SENS_0: R0.1, S0.3, U1.14
SENS_1: R1.1, S1.3, U1.13
SENS_2: R2.1, S2.3, U2.14
SENS_3: R3.1, S3.3, U2.13
SENS_4: R4.1, S4.3, U1.12
SENS_5: R5.1, S5.3, U1.11
SENS_6: R6.1, S6.3, U2.12
SENS_7: R7.1, S7.3, U2.11
SENS_8: R8.1, S8.3, U1.3
SENS_9: R9.1, S9.3, U1.4
SENS_10: R10.1, S10.3, U2.3
SENS_11: R11.1, S11.3, U2.4
SENS_12: R12.1, S12.3, U1.5
SENS_13: R13.1, S13.3, U1.6
SENS_14: R14.1, S14.3, U2.5
SENS_15: R15.1, S15.3, U2.6
SER_IN: J1.6, U1.10
SER_MID: U1.9, U2.10
SER_OUT: J2.6, U2.9

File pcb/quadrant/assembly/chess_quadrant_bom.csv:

Item Number,Item Description,Manufacturer Part Number,Value,Package,Designator,Quantity,Assembly Instructions
1,"Hall effect sensor, digital, TO-92",A3144E,A3144,TO-92,"S0,S1,S2,S3,S4,S5,S6,S7,S8,S9,S10,S11,S12,S13,S14,S15",16,"MOUNT ON BOTTOM SIDE, flush to board. CRITICAL: mirror-pinout clones - insert 180deg rotated vs standard: TEXT/printed side of package faces the FLAT side of silk outline. Solder ONE at S0 first, power 5V + magnet test (output pulls low), confirm with customer before soldering the rest. See ASSEMBLY_NOTES.md"
2,"Resistor 10k Ohm 1/4W 5% axial",CFR-25JB-52-10K,10k,Axial DIN0207 P10.16mm,"R0,R1,R2,R3,R4,R5,R6,R7,R8,R9,R10,R11,R12,R13,R14,R15",16,Top side. Not polarized
3,"Ceramic disc capacitor 100nF 50V",K104K15X7RF53L2,100n,Disc D5.0mm P5.00mm,"C0,C1,C2,C3,C4,C5,C6,C7,C8,C9",10,Top side. Not polarized
4,"8-bit parallel-load shift register, DIP-16",SN74HC165N,74HC165,DIP-16 W7.62mm,"U1,U2",2,Top side. Pin-1 notch matches silkscreen notch
5,"Pin header male 1x6 2.54mm vertical, through-hole",PRPC006SAAN-RC,1x6 header,PinHeader 1x06 P2.54mm,J1,1,Top side. Vertical
6,"Pin header male 1x6 2.54mm vertical, through-hole",PRPC006SAAN-RC,1x6 header,PinHeader 1x06 P2.54mm,J2,1,Top side. Vertical
